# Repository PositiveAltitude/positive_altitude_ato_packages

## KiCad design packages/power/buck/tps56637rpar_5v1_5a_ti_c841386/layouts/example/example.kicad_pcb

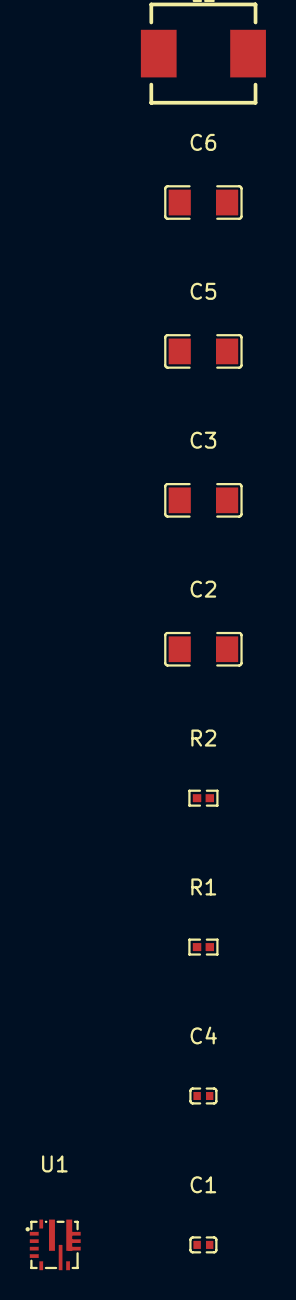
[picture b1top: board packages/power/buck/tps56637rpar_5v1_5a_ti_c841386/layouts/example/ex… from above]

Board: 2 copper layers, 10 parts (0 on the bottom side), 6 nets, no tracks yet.

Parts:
C1, C4: 0F; C0402
C2, C3, C5, C6: 0F; C1206
L1: L 0H; IND-SMD_L7.0-W6.6
R1: 10000Ω; R0402
R2: 75000Ω; R0402
U1: VQFN-HR-10_L3.0-W3.0_RPA

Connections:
FB: R1.1, R2.2, U1.2
hv: C1.1, U1.7
input_bypass-power-hv: C2.1, C3.1, C4.1, U1.8
lv: C1.2, L1.1, U1.6
output_bulk_b-power-hv: C5.1, C6.1, L1.2, R2.1
output_bulk_b-power-lv: C2.2, C3.2, C4.2, C5.2, C6.2, R1.2, U1.3, U1.9

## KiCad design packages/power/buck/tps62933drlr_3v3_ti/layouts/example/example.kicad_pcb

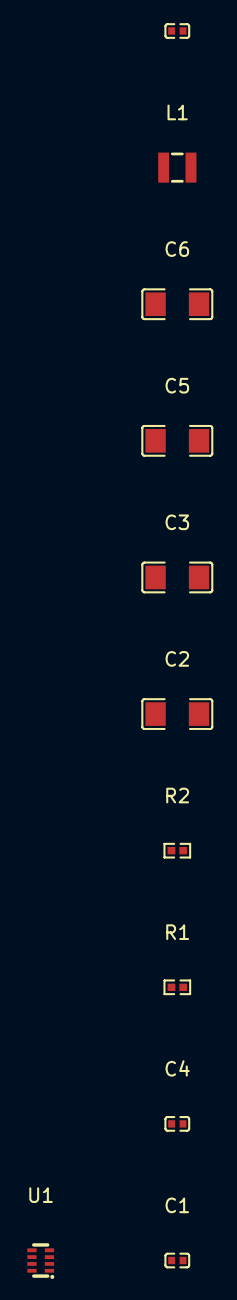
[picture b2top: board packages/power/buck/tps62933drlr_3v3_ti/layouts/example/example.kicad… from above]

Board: 2 copper layers, 11 parts (0 on the bottom side), 7 nets, no tracks yet.

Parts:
C1, C4, C7: C0402
C2, C3, C5, C6: C1206
L1: IND-SMD_L2.5-W2.0_MHCHL2520
R1, R2: R0402
U1: SOT-583-8_L2.1-W1.2-P0.50-LS1.6-BR

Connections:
BST: C1.1, U1.6
FB: R1.1, R2.2, U1.8
GND: C2.2, C3.2, C4.2, C5.2, C6.2, C7.2, R1.2, U1.1, U1.4
SS: C7.1, U1.7
SW: C1.2, L1.1, U1.5
VIN: C2.1, C3.1, C4.1, U1.2, U1.3
hv: C5.1, C6.1, L1.2, R2.1

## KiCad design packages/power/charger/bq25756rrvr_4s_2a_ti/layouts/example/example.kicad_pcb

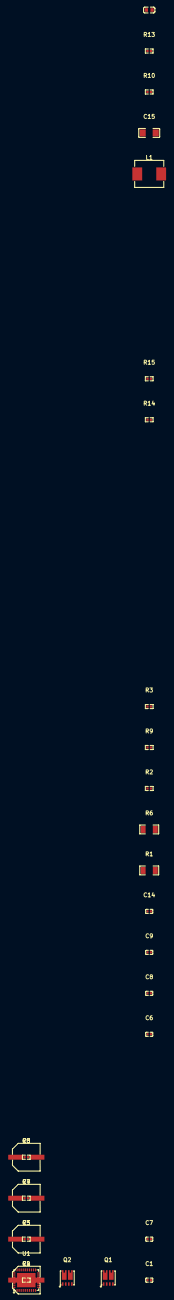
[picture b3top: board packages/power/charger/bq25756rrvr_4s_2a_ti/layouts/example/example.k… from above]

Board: 2 copper layers, 29 parts (0 on the bottom side), 23 nets, no tracks yet.

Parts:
C1, C6, C7, C8, C9, C14: C0402
C2, C3, C4, C5: CAP-SMD_BD6.3-L6.6-W6.6-FD
C15: C1206
C16: C0603
L1: IND-SMD_L7.1-W6.6_SLO0650H
Q1, Q2: DFN-8_L3.3-W3.3-P0.75-TL
R1, R6: R1206
R2, R3, R4, R5, R7, R8, R9, R10, R13, R14, R15: R0402
U1: TQFN-36_L6.0-W5.0-P0.50-BL-EP-1

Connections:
1: C4.1, C14.1, C16.1, Q2.8, R4.1, R6.2, U1.32, U1.33, U1.34
2: C9.2, L1.2, Q1.1, Q1.5, U1.18
19: Q1.2, U1.19
21: Q1.4, U1.21
25: Q2.4, U1.25
FB: R9.1, R10.2, U1.12
FSW_SYNC: R13.1, U1.36
ICHG: R2.1, U1.9
TS: R14.1, R15.2, U1.8
acn_filtered: C1.2, R4.2, U1.29
acp_filtered: C1.1, R5.2, U1.30
battery-hv: C3.1, R1.2, R7.1, R10.1
charger-1: C2.1, C6.1, Q1.8, R1.1, R8.1
charger-1-1: C8.1, U1.26
charger-1-2: C8.2, L1.1, Q2.1, Q2.5, U1.28
charger-1-3: C9.1, U1.20
charger-1-4: C15.1, R15.1, U1.23, U1.24
charger-2: Q2.2, U1.27
hv: C5.1, R5.1, R6.1
lv: C2.2, C3.2, C4.2, C5.2, C6.2, C14.2, C15.2, C16.2, Q1.3, Q2.3, R2.2, R3.2, R9.2, R13.2, R14.2, U1.10, U1.11, U1.17, U1.22, U1.35, U1.37
nCE: R3.1, U1.7
srn_filtered: C7.2, R7.2, U1.13
srp_filtered: C7.1, R8.2, U1.14

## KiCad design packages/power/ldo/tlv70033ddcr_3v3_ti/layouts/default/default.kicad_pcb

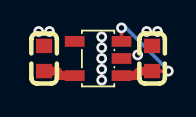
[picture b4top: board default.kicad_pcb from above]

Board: 2 copper layers, 3 parts (0 on the bottom side), 3 nets.

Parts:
C1, C2: C0603
U1: SOT-23-5_L3.0-W1.7-P0.95-LS2.8-BR

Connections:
hv: C1.1, U1.1, U1.3
lv: C1.2, C2.2, U1.2
power_out-hv: C2.1, U1.5
